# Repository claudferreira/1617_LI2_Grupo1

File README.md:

# 1617_LI2_Grupo1
Projeto laboratorios integrados II

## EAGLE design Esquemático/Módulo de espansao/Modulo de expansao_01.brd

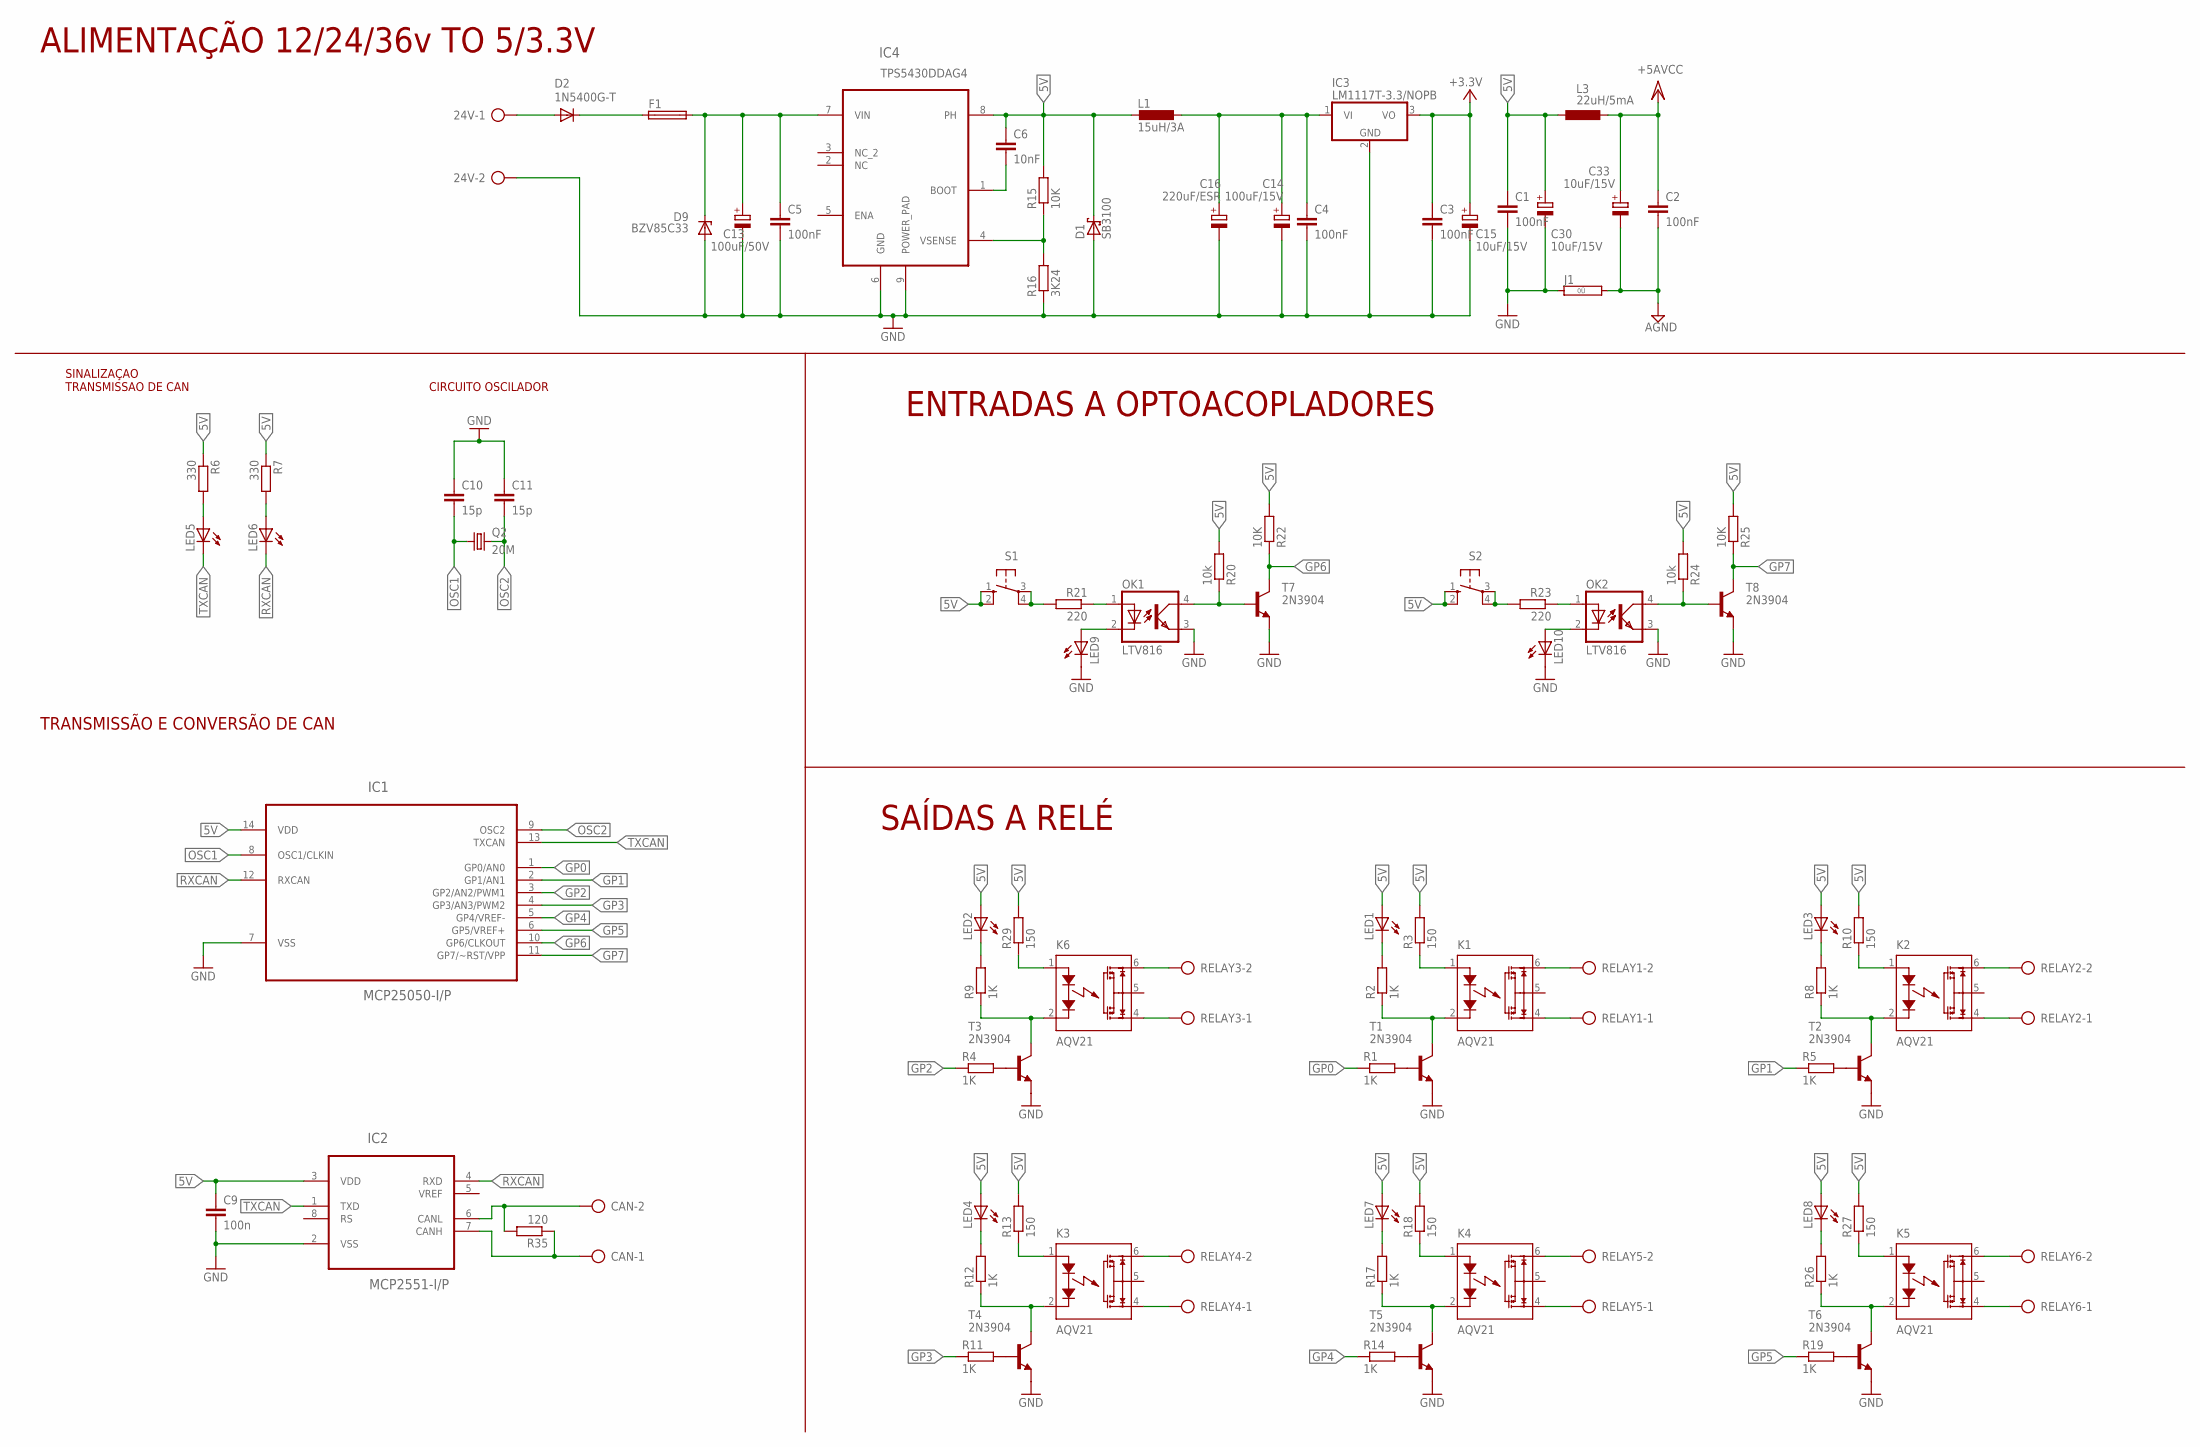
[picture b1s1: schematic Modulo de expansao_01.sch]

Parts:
24V: AK300/2
C1, C2, C3, C4, C5: 100nF; C050-024X044
C6: 10nF; C025-025X050
C9: 100n; C050-024X044
C10, C11: 15p; C025-024X044
C13: 100uF/50V; E3,5-10
C14: 100uF/15V; E2-5
C15: 10uF/15V; E2-5
C16: 220uF/ESR; E2,5-7
C30, C33: 10uF/15V; E2,5-6
CAN: AK300/2
D1: SB3100; DO201T15
D2: 1N5400G-T; DO201-15
D9: BZV85C33; DO34Z7
F1: TR5
IC1: MCP25050-I/P; DIP254P762X432-14
IC2: MCP2551-I/P; DIP254P762X432-8
IC3: LM1117T-3.3/NOPB; TO220H
IC4: TPS5430DDAG4; SOIC127P600X170-9N
J1: 0R; 0R/10
K1, K2, K3, K4, K5, K6: AQV21; DIL06
L1: 15uH/3A; 6000-XXXX-RC
L3: 22uH/5mA; 6000-XXXX-RC
LED1, LED2, LED3, LED4, LED5, LED6, LED7, LED8, LED9, LED10: LED3MM
OK1, OK2: LTV816; DIL04
Q2: 20M; HC49/S
R1, R2, R4, R5, R8, R9, R11, R12, R14, R17, R19, R26: 1K; 0207/10
R3, R10, R13, R18, R27, R29: 150; 0207/10
R6, R7: 330; 0207/10
R15, R22, R25: 10K; 0207/10
R16: 3K24; 0207/10
R20, R24: 10k; 0207/10
R21, R23: 220; 0207/10
R35: 120; 0207/10
RELAY1, RELAY2, RELAY3, RELAY4, RELAY5, RELAY6: AK300/2
S1, S2: 10-XX; B3F-10XX
T1, T2, T3, T4, T5, T6, T7, T8: 2N3904; TO92

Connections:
5V: C1.1, C6.1, C9.1, C30.+, D1.C, IC1.14 (VDD), IC2.3 (VDD), IC4.8 (PH), L1.2, L3.1, LED1.A, LED2.A, LED3.A, LED4.A, LED7.A, LED8.A, R3.2, R6.1, R7.1, R10.2, R13.2, R15.2, R18.2, R20.2, R22.2, R24.2, R25.2, R27.2, R29.2, S1.1 (S), S1.2 (S1), S2.1 (S), S2.2 (S1)
24V: 24V.1, D2.A
+3.3V: C3.1, C15.+, IC3.3 (VO)
AGND: C2.2, C33.-, J1.2
GND: 24V.2, C1.2, C3.2, C4.2, C5.2, C9.2, C10.1, C11.1, C13.-, C14.-, C15.-, C16.-, C30.-, D1.A, D9.A, IC1.7 (VSS), IC2.2 (VSS), IC3.2 (GND), IC4.6 (GND), IC4.9 (POWER_PAD), J1.1, LED9.K (C), LED10.K (C), OK1.3 (EMIT), OK2.3 (EMIT), R16.1, T1.3 (E), T2.3 (E), T3.3 (E), T4.3 (E), T5.3 (E), T6.3 (E), T7.3 (E), T8.3 (E)
GP0: IC1.1 (GP0/AN0), R1.1
GP1: IC1.2 (GP1/AN1), R5.1
GP2: IC1.3 (GP2/AN2/PWM1), R4.1
GP3: IC1.4 (GP3/AN3/PWM2), R11.1
GP4: IC1.5 (GP4/VREF-), R14.1
GP5: IC1.6 (GP5/VREF+), R19.1
GP6: IC1.10 (GP6/CLKOUT), R22.1, T7.1 (C)
GP7: IC1.11 (GP7/~RST/VPP), R25.1, T8.1 (C)
unnamed: LED1.K (C), R2.2
unnamed: K1.2 (K), R2.1, T1.1 (C)
unnamed: R1.2, T1.2 (B)
unnamed: K1.6 (D1), RELAY1.2
unnamed: K1.4 (D2), RELAY1.1
unnamed: LED3.K (C), R8.2
unnamed: K2.2 (K), R8.1, T2.1 (C)
unnamed: R5.2, T2.2 (B)
unnamed: K2.6 (D1), RELAY2.2
unnamed: R4.2, T3.2 (B)
unnamed: LED2.K (C), R9.2
unnamed: K6.2 (K), R9.1, T3.1 (C)
unnamed: K6.6 (D1), RELAY3.2
unnamed: K6.4 (D2), RELAY3.1
unnamed: K2.4 (D2), RELAY2.1
unnamed: LED4.K (C), R12.2
unnamed: K3.2 (K), R12.1, T4.1 (C)
unnamed: R11.2, T4.2 (B)
unnamed: K3.6 (D1), RELAY4.2
unnamed: K3.4 (D2), RELAY4.1
unnamed: C5.1, C13.+, D9.C, F1.2, IC4.7 (VIN)
unnamed: LED7.K (C), R17.2
unnamed: D2.C, F1.1
unnamed: LED5.A, R6.2
unnamed: LED6.A, R7.2
unnamed: K4.2 (K), R17.1, T5.1 (C)
unnamed: R14.2, T5.2 (B)
unnamed: K4.6 (D1), RELAY5.2
unnamed: K4.4 (D2), RELAY5.1
unnamed: LED8.K (C), R26.2
unnamed: CAN.2, IC2.6 (CANL), R35.2
unnamed: CAN.1, IC2.7 (CANH), R35.1
unnamed: K5.2 (K), R26.1, T6.1 (C)
unnamed: R19.2, T6.2 (B)
unnamed: K5.6 (D1), RELAY6.2
unnamed: K5.4 (D2), RELAY6.1
unnamed: OK1.4 (COL), R20.1, T7.2 (B)
unnamed: R23.2, S2.3, S2.4 (P1)
unnamed: OK2.1 (A), R23.1
unnamed: OK2.4 (COL), R24.1, T8.2 (B)
unnamed: LED9.A, OK1.2 (C)
unnamed: LED10.A, OK2.2 (C)
unnamed: K2.1 (A), R10.1
unnamed: K4.1 (A), R18.1
unnamed: K1.1 (A), R3.1
unnamed: K3.1 (A), R13.1
unnamed: K5.1 (A), R27.1
unnamed: K6.1 (A), R29.1
unnamed: R21.2, S1.3, S1.4 (P1)
unnamed: OK1.1 (A), R21.1
unnamed: C4.1, C14.+, C16.+, IC3.1 (VI), L1.1
unnamed: C6.2, IC4.1 (BOOT)
unnamed: IC4.4 (VSENSE), R15.1, R16.2
OSC1: C10.2, IC1.8 (OSC1/CLKIN), Q2.1
OSC2: C11.2, IC1.9 (OSC2), Q2.2
RXCAN: IC1.12 (RXCAN), IC2.4 (RXD), LED6.K (C)
TXCAN: IC1.13 (TXCAN), IC2.1 (TXD), LED5.K (C)
VCC/2: C2.1, C33.+, L3.2

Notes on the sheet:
CIRCUITO OSCILADOR
SINALIZAÇAO TRANSMISSAO DE CAN
ALIMENTAÇÃO 12/24/36v TO 5/3.3V
SAÍDAS A RELÉ
ENTRADAS A OPTOACOPLADORES
TRANSMISSÃO E CONVERSÃO DE CAN

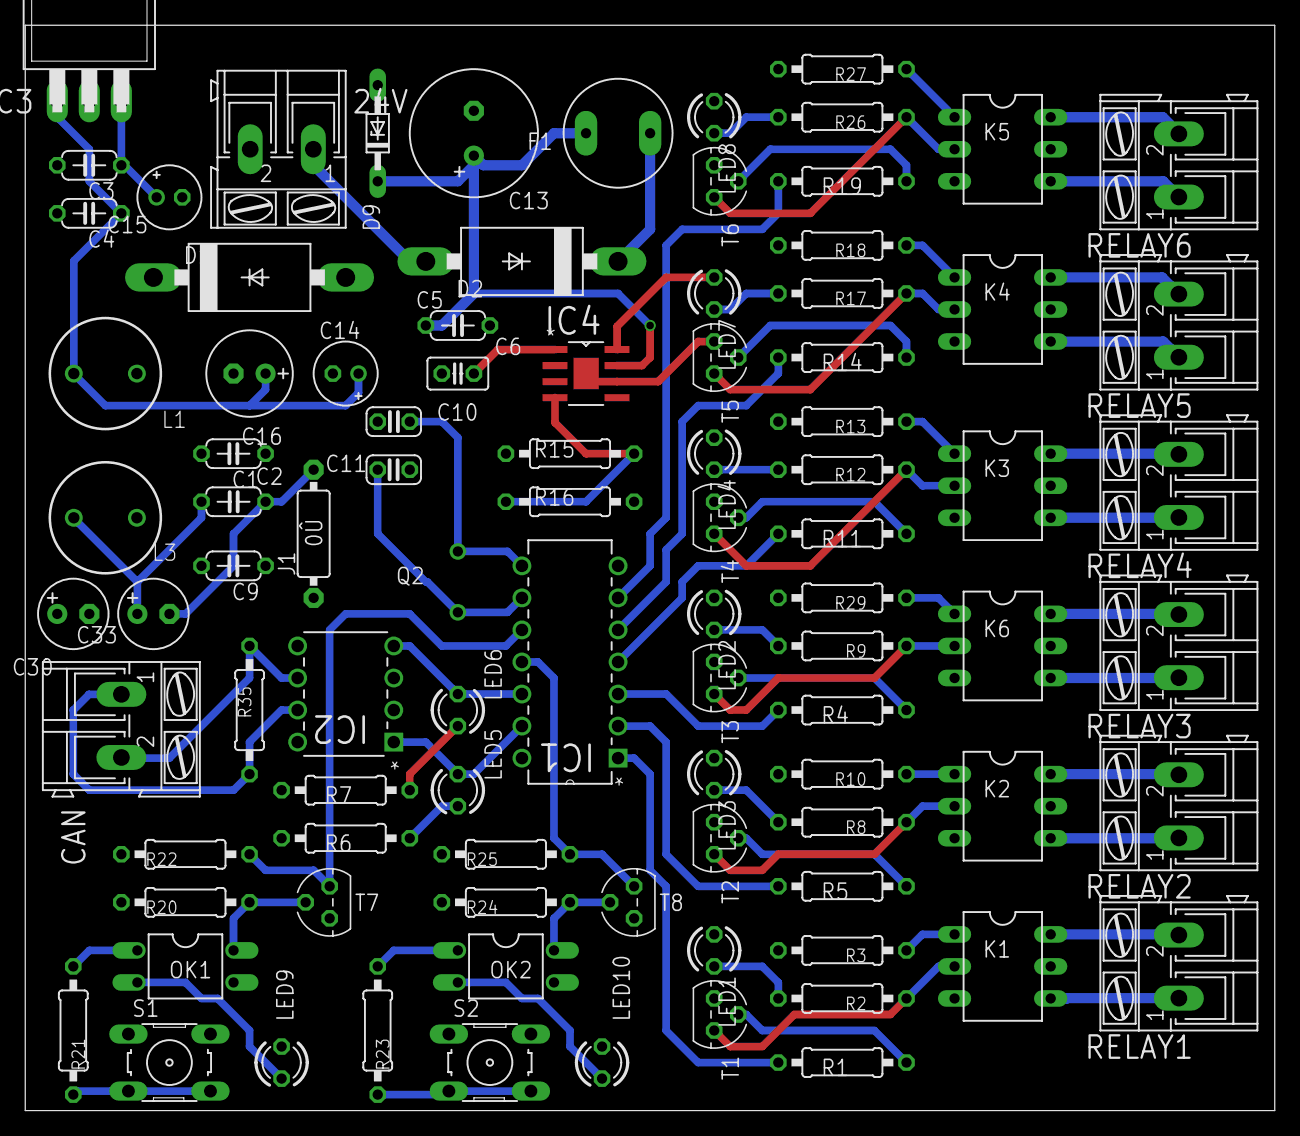
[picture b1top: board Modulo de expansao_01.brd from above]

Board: 2 copper layers, 99.0 x 86.0 mm, 92 parts (1 on the bottom side), 71 nets.

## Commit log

2017-04-19 inicio projecto
2017-04-19 Revert "inicio projecto"
    This reverts commit 3b4c43085cb87a7cdb590b9d2af61c07694af5ac.
2017-04-25 V0.1
    Falta incluir circuito com atmega
2017-04-26 Escolhas estratégicas
2017-04-26 README.md
2017-04-26 Planificacao
    Escolhas estratégicas
2017-04-26 Diagrama de blocos
2017-05-06 apagar esquema
2017-05-06 Esqema para expander
    Em trabalho
2017-05-06 Circuito Módulo expansão i/o CAN
    tem MCP25050 e MCP2551
    2 ENTRADAS E 6 SAIDAS
2017-05-07 alterado parte das saídas a rele
    foi colocado 24v às saídas de rele, e o sinalizador na parte de comando
2017-05-07 Create Esquemático do Master
2017-05-08 Correçao no modulo de expansao e alteraçao de nomes dos ficheiros
    No modulo de expansao, passei tudo para thro hole e comecei já a fazer
    pcb. enviei para o isaias por email para ver se quer alterar alguma
    coisa
2017-05-12 alteraçao modulo expansao
    Ainda em falta sinalizaçao nas entradas a optos, de resto tudo OK
2017-05-21 Entradas e saidas testadas no modulo de expansao.
    Falta somente testar as ligaçoes no que se refere à comunicação
2017-05-24 Módulo de interface com o utilizador
    Início da programação do módulo de interface com o utilizador com
    detecção de faces e criação dos ecrãs principal e dashboard.
2017-05-27 Deteção e reconhecimento da face. Criação de ecrã de perfis.
    Aperfeiçoamento dos ecrãs principal e dashboard e criação de ecrã de
    gestão de perfis. Criação da fase de treino para reconhecimento de
    faces/utilizadores e gravação de dados em BD no formato json.
2017-06-04 actualizaçao esquematico e brd do modulo expansao
    versoes finais do modulo espansao, do esquematico e board
2017-06-10 modulo de expansao final
2017-07-24 Várias alterações
2017-07-26 Pequenas alterações
    Algumas correções
2017-07-28 Inclusao codigo master e slave + aplicaçao testes
    codigos dos arduinos, e de testes para comprovar comunicaçao
2017-07-28 Final Esquematic
2017-07-28 Relatório versão final
2017-07-31 Introduçao do relatorio final
2017-07-31 Revert "Introduçao do relatorio final"
    This reverts commit d45dd00f4f8dcfc3cb2f5f705d903aa68f92cd70.
